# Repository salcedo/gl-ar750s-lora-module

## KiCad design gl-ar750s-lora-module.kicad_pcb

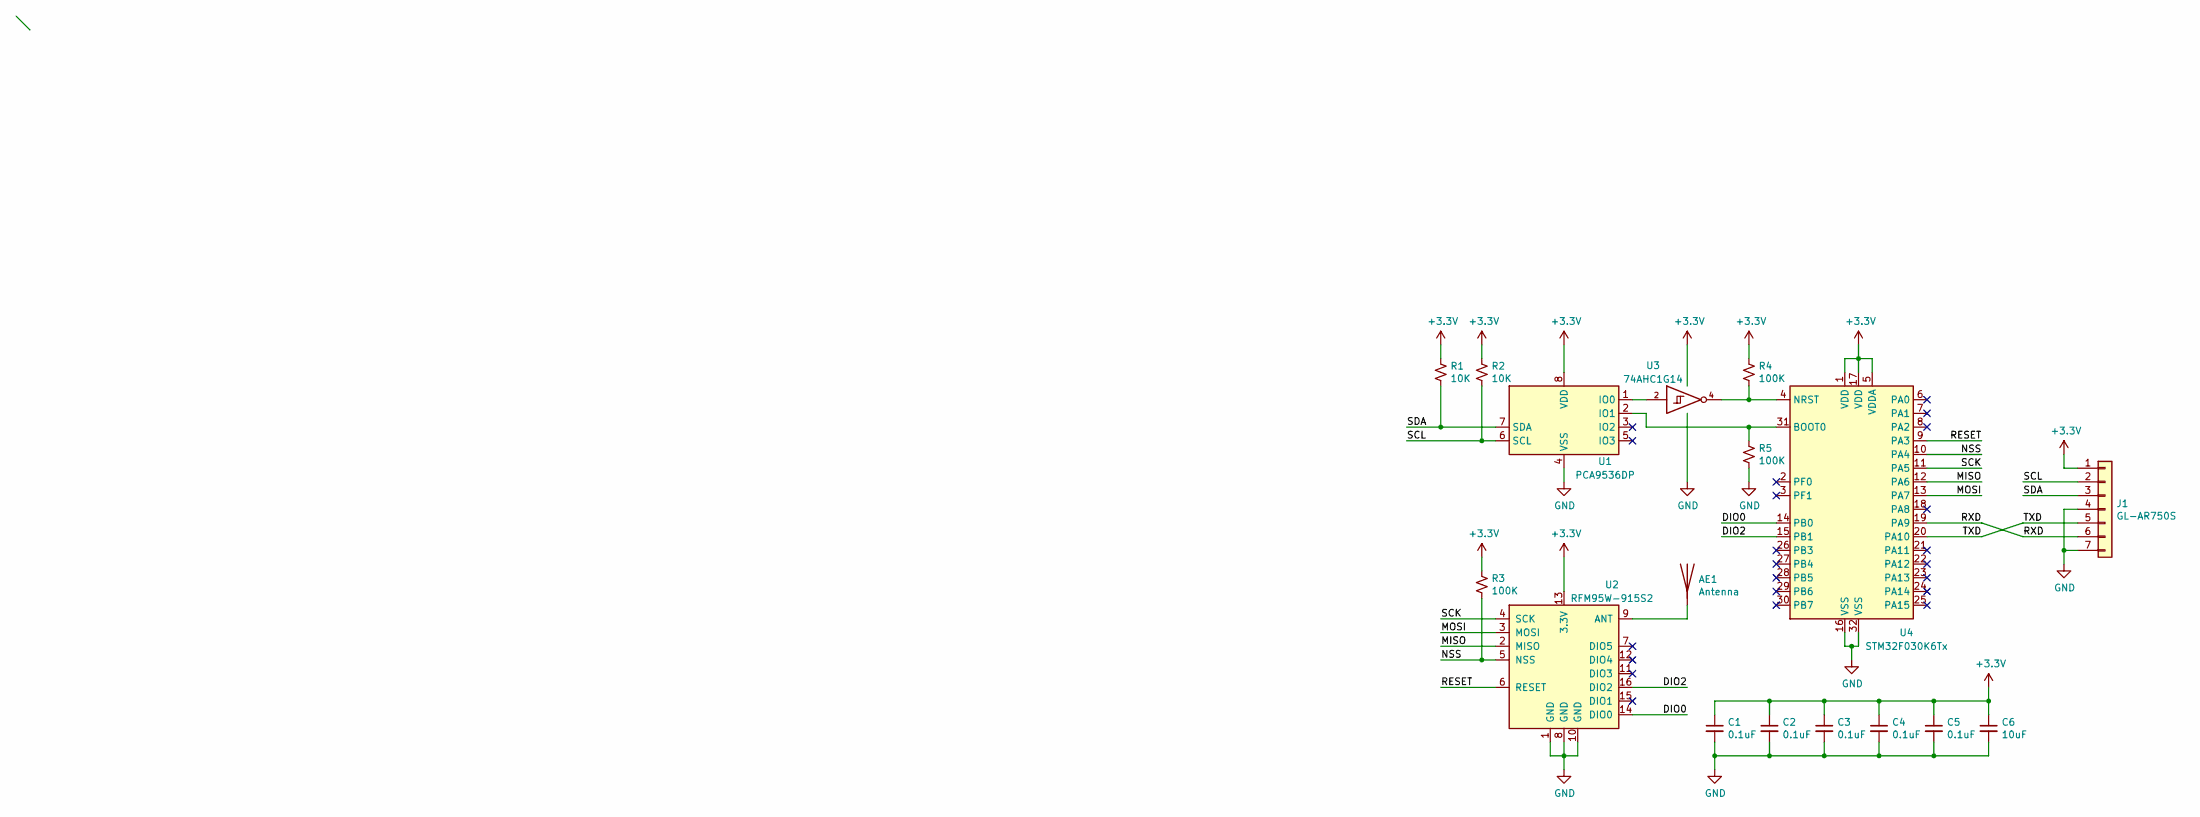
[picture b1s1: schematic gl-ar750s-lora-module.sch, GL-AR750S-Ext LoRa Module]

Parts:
AE1: Antenna; PinHeader_1x01_P2.54mm_Vertical
C1, C2, C3, C4, C5: 0.1uF; C_0805_2012Metric
C6: 10uF; C_1206_3216Metric
J1: GL-AR750S; PinHeader_1x07_P2.54mm_Vertical
R1, R2: 10K; R_0805_2012Metric
R3, R4, R5: 100K; R_0805_2012Metric
U1: PCA9536DP; TSSOP-8_3x3mm_P0.65mm
U2: RFM95W-915S2; HOPERF_RFM9XW_SMD
U3: 74AHC1G14; SOT-353_SC-70-5
U4: STM32F030K6Tx; LQFP-32_7x7mm_P0.8mm

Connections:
+3V3: C1.1, C2.1, C3.1, C4.1, C5.1, C6.1, J1.1, R1.1, R2.1, R3.1, R4.1, U1.8 (VDD), U2.13 (3.3V), U3.5 (VCC), U4.1 (VDD), U4.5 (VDDA), U4.17 (VDD)
/DIO0: U2.14 (DIO0), U4.14 (PB0)
/DIO2: U2.16 (DIO2), U4.15 (PB1)
/MISO: U2.2 (MISO), U4.12 (PA6)
/MOSI: U2.3 (MOSI), U4.13 (PA7)
/NSS: R3.2, U2.5 (NSS), U4.10 (PA4)
/RESET: U2.6 (RESET), U4.9 (PA3)
/RXD: J1.6, U4.19 (PA9)
/SCK: U2.4 (SCK), U4.11 (PA5)
/SCL: J1.2, R2.2, U1.6 (SCL)
/SDA: J1.3, R1.2, U1.7 (SDA)
/TXD: J1.5, U4.20 (PA10)
GND: C1.2, C2.2, C3.2, C4.2, C5.2, C6.2, J1.4, J1.7, R5.2, U1.4 (VSS), U2.1 (GND), U2.8 (GND), U2.10 (GND), U3.3 (GND), U4.16 (VSS), U4.32 (VSS)
unnamed: AE1.1, U2.9 (ANT)
unnamed: R4.2, U3.4, U4.4 (NRST)
unnamed: R5.1, U1.2 (IO1), U4.31 (BOOT0)
unnamed: U1.1 (IO0), U3.2

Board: 2 copper layers, 16 parts (2 on the bottom side), 16 nets, no tracks yet.

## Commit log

2024-10-27 for archive
